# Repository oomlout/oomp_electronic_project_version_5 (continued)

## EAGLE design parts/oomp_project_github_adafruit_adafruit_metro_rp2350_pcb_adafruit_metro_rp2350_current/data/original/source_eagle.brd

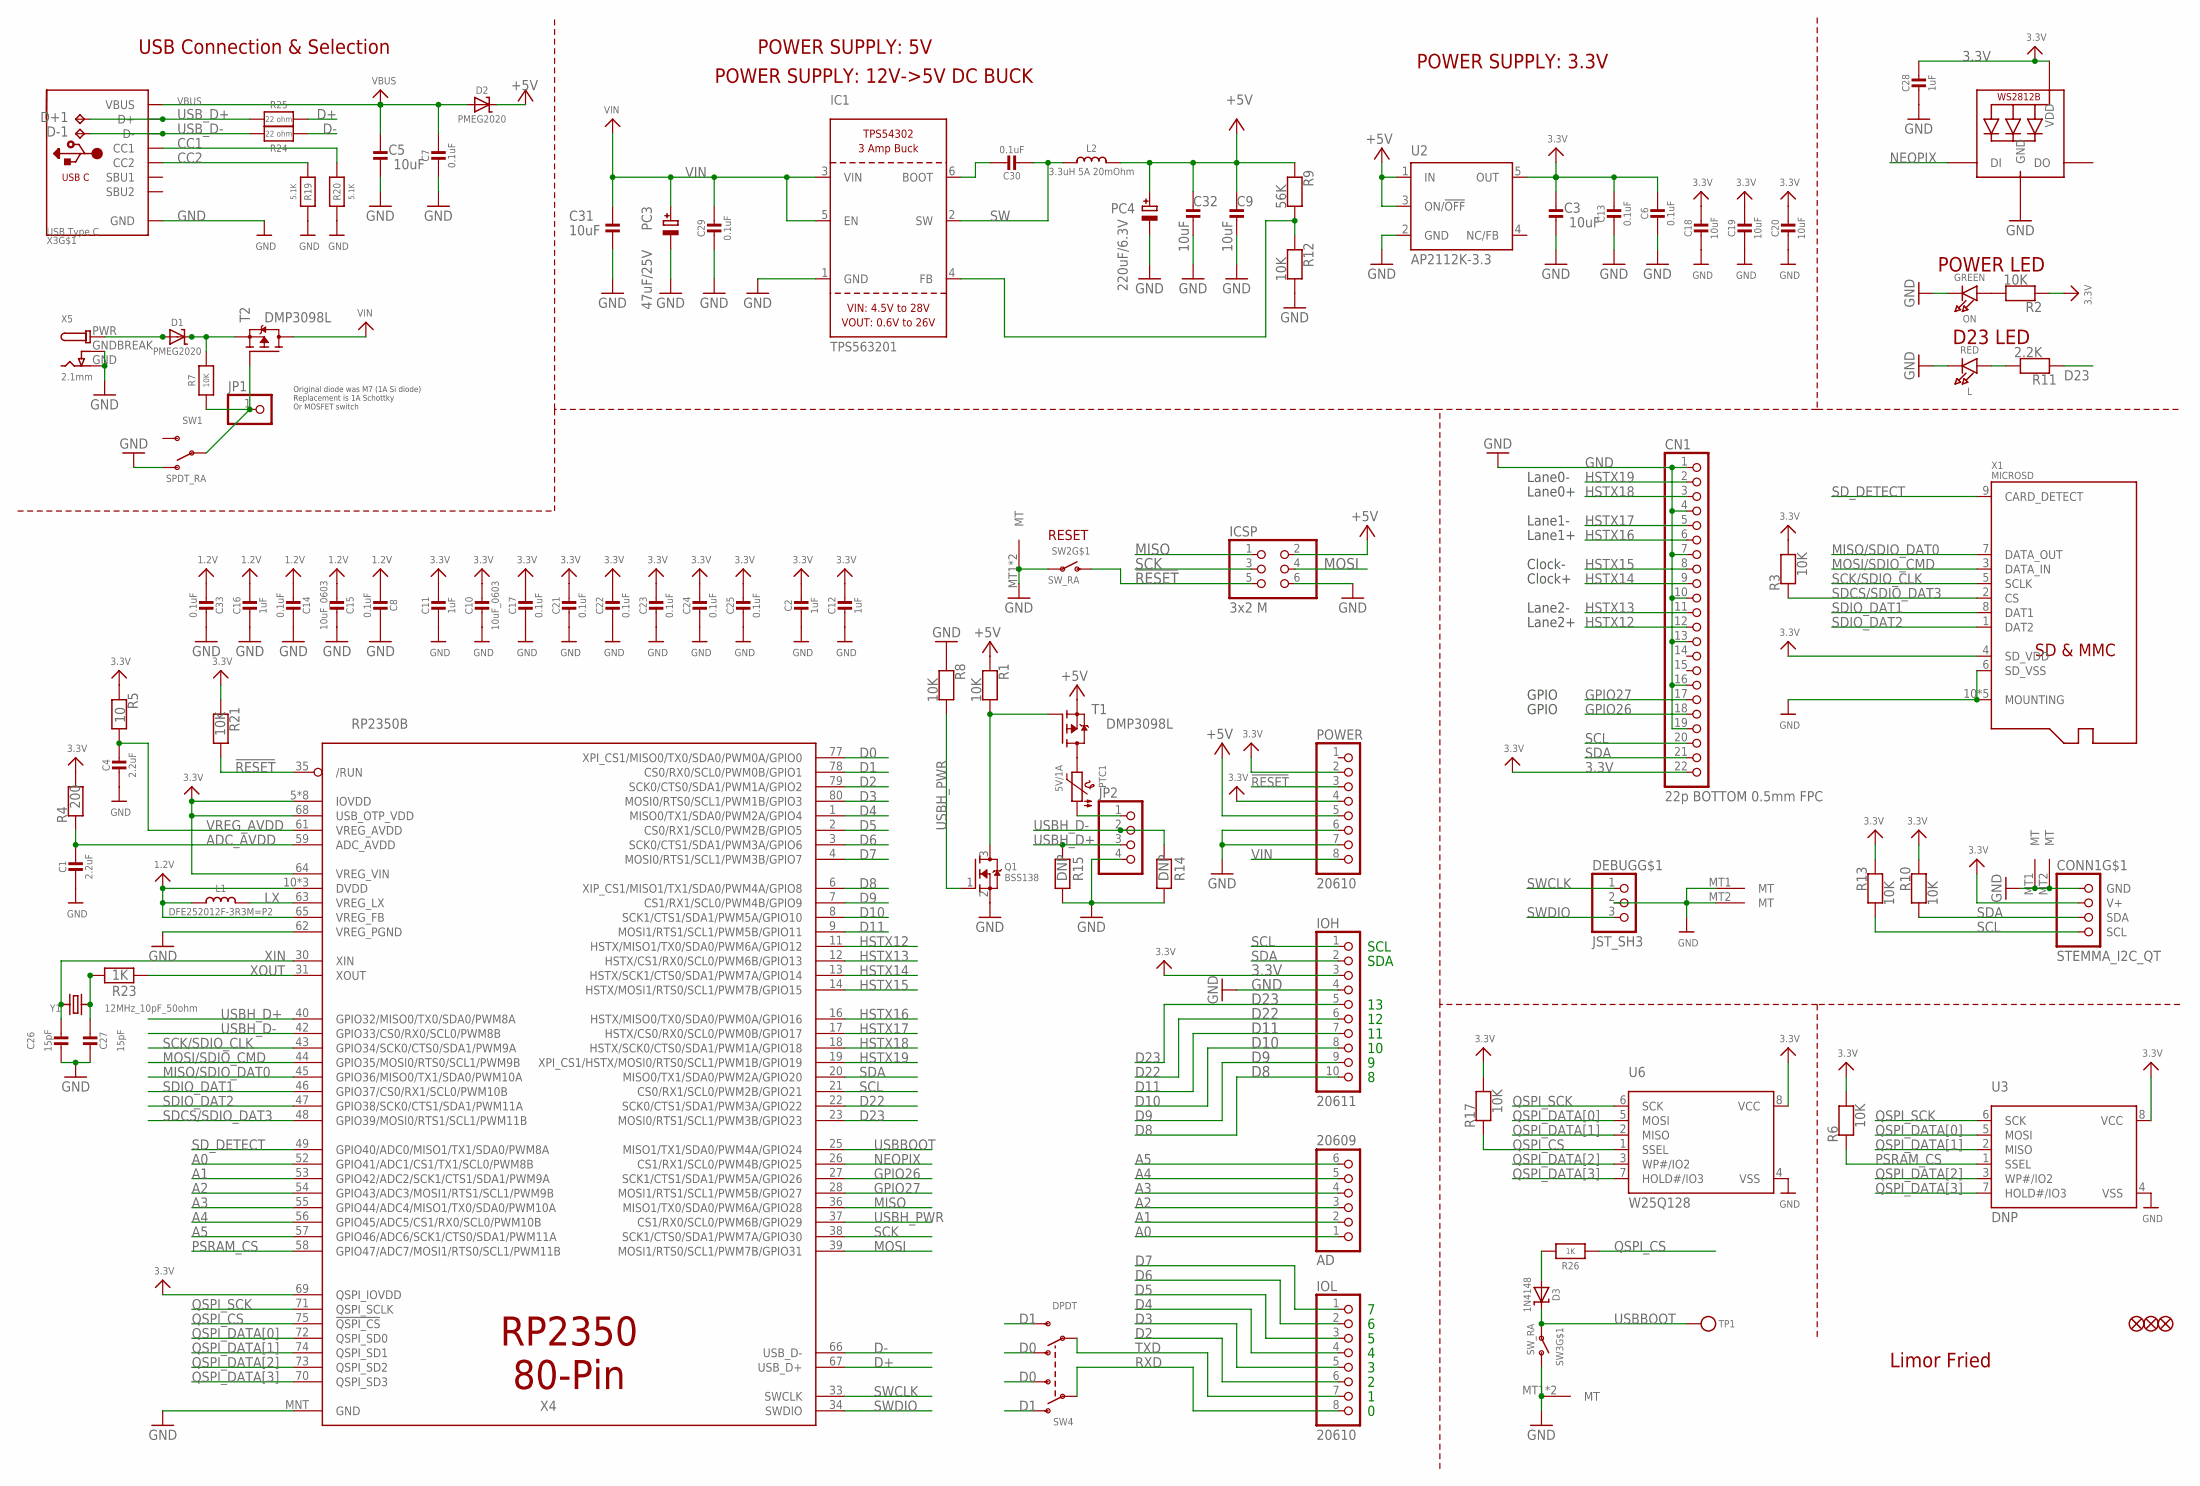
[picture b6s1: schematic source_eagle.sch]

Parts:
AD: 20609; 1X06_OVALWAVE
C1, C4: 2.2uF; 0603-NO
C2, C11, C12, C16, C28: 1uF; 0603-NO
C3, C5, C9, C18, C19, C20, C31, C32: 10uF; 0805-NO
C6, C7, C8, C13, C14, C17, C21, C22, C23, C24, C25, C29, C30, C33: 0.1uF; 0603-NO
C10, C15: 10uF_0603; 0603-NO_WIDE
C26, C27: 15pF; 0603-NO
CN1: 22p BOTTOM 0.5mm FPC; FPC_22PIN
CONN1: STEMMA_I2C_QT; JST_SH4
D1, D2: PMEG2020; SOD-323
D3: 1N4148; SOD-323
D+1: TPB1,27; B1,27
D-1: TPB1,27; B1,27
DEBUG: JST_SH3; JST_SH3_RA
FD1, FD2, FD3: FIDUCIAL_1MM
IC1: TPS563201; SOT23-6
ICSP: 3x2 M; 2X03_ROUND_70MIL
IOH: 20611; 1X10_OVALWAVE
IOL: 20610; 1X08_OVALWAVE
JP1: HEADER-1X1ROUND; 1X01_ROUND
JP2: HEADER-1X4ROUND; 1X04_ROUND
L: RED; CHIPLED_0603_NOOUTLINE
L1: DFE252012F-3R3M=P2; INDUCTOR_1007
L2: 3.3uH 5A 20mOhm; INDUCTOR_0603S
LED2: WS2812B_3535FULL; LED3535_FULLPADS
ON: GREEN; CHIPLED_0603_NOOUTLINE
PC3: 47uF/25V; PANASONIC_D
PC4: 220uF/6.3V; PANASONIC_D
POWER: 20610; 1X08_OVALWAVE
PTC1: 5V/1A; 0805-NO
Q1: BSS138; SOT23-WIDE
R1, R2, R3, R6, R7, R8, R10, R12, R13, R17, R21: 10K; 0603-NO
R4: 200; 0603-NO
R5: 10; 0603-NO
R9: 56K; 0603-NO
R11: 2.2K; 0603-NO
R14, R15: DNP; 0603-NO
R19, R20: 5.1K; 0603-NO
R23, R26: 1K; 0603-NO
R24, R25: 22 ohm; 0603-NO
SW1: SPDT_RA; SPDT_SMT_SSSS811101
SW2, SW3: SW_RA; SPST_TACTILE_RA
SW4: DPDT; EG1390
T1, T2: DMP3098L; SOT23-WIDE
TP1: TESTPOINTROUND1.5MMNO; TESTPOINT_ROUND_1.5MM_NO
U2: AP2112K-3.3; SOT23-DBV
U3: DNP; SOIC8_208MIL
U6: W25Q128; SOIC8_208MIL
X1: MICROSD; MOLEX_104031-0811
X3: USB Type C; USB_C_CUSB31-CFM2AX-01-X
X4: RP2350B; QFN80
X5: 2.1mm; DCJACK_2MM_PTH
Y1: 12MHz_10pF_50ohm; CRYSTAL_2.5X2

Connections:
1.2V: C8.2, C14.2, C15.2, C16.1, C33.2, L1.P$1 (1), X4.10 (DVDD), X4.32 (DVDD), X4.51 (DVDD), X4.65 (VREG_FB)
3.3V: C2.1, C3.2, C6.2, C10.1, C11.1, C12.1, C13.1, C17.1, C18.1, C19.1, C20.1, C21.1, C22.1, C23.1, C24.1, C25.1, C28.1, CN1.22, CONN1.2 (V+), IOH.3, LED2.2 (VDD), POWER.2, POWER.4, R2.1, R3.2, R4.2, R5.1, R6.2, R10.1, R13.1, R17.2, R21.1, U2.5 (OUT), U3.8 (VCC), U6.8 (VCC), X1.4 (SD_VDD), X4.5 (IOVDD), X4.15 (IOVDD), X4.24 (IOVDD), X4.29 (IOVDD), X4.41 (IOVDD), X4.50 (IOVDD), X4.60 (IOVDD), X4.64 (VREG_VIN), X4.68 (USB_OTP_VDD), X4.69 (QSPI_IOVDD), X4.76 (IOVDD)
!RESET: ICSP.5, POWER.3, R21.2, SW2.2 (S), X4.35 (/RUN)
+5V: C9.2, C32.2, D2.C, ICSP.2, L2.P$2 (2), PC4.+, POWER.5, R1.1, R9.1, T1.2 (S), U2.1 (IN), U2.3 (ON/!OFF)
A0: AD.1, X4.52 (GPIO41/ADC1/CS1/TX1/SCL0/PWM8B)
A1: AD.2, X4.53 (GPIO42/ADC2/SCK1/CTS1/SDA1/PWM9A)
A2: AD.3, X4.54 (GPIO43/ADC3/MOSI1/RTS1/SCL1/PWM9B)
A3: AD.4, X4.55 (GPIO44/ADC4/MISO1/TX0/SDA0/PWM10A)
A4: AD.5, X4.56 (GPIO45/ADC5/CS1/RX0/SCL0/PWM10B)
A5: AD.6, X4.57 (GPIO46/ADC6/SCK1/CTS0/SDA1/PWM11A)
ADC_AVDD: C1.1, R4.1, X4.59 (ADC_AVDD)
CC1: R20.2, X3.A5 (CC1)
CC2: R19.2, X3.B5 (CC2)
D0: SW4.O2, SW4.S1, X4.77 (XPI_CS1/MISO0/TX0/SDA0/PWM0A/GPIO0)
D1: SW4.O1, SW4.S2, X4.78 (CS0/RX0/SCL0/PWM0B/GPIO1)
D2: IOL.6, X4.79 (SCK0/CTS0/SDA1/PWM1A/GPIO2)
D3: IOL.5, X4.80 (MOSI0/RTS0/SCL1/PWM1B/GPIO3)
D4: IOL.4, X4.1 (MISO0/TX1/SDA0/PWM2A/GPIO4)
D5: IOL.3, X4.2 (CS0/RX1/SCL0/PWM2B/GPIO5)
D6: IOL.2, X4.3 (SCK0/CTS1/SDA1/PWM3A/GPIO6)
D7: IOL.1, X4.4 (MOSI0/RTS1/SCL1/PWM3B/GPIO7)
D8: IOH.10, X4.6 (XIP_CS1/MISO1/TX1/SDA0/PWM4A/GPIO8)
D9: IOH.9, X4.7 (CS1/RX1/SCL0/PWM4B/GPIO9)
D10: IOH.8, X4.8 (SCK1/CTS1/SDA1/PWM5A/GPIO10)
D11: IOH.7, X4.9 (MOSI1/RTS1/SCL1/PWM5B/GPIO11)
D22: IOH.6, X4.22 (SCK0/CTS1/SDA1/PWM3A/GPIO22)
D23: IOH.5, R11.1, X4.23 (MOSI0/RTS1/SCL1/PWM3B/GPIO23)
D+: R25.2, X4.67 (USB_D+)
D-: R24.2, X4.66 (USB_D-)
GND: C1.2, C2.2, C3.1, C4.2, C5.1, C6.1, C7.2, C8.1, C9.1, C10.2, C11.2, C12.2, C13.2, C14.1, C15.1, C16.2, C17.2, C18.2, C19.2, C20.2, C21.2, C22.2, C23.2, C24.2, C25.2, C26.1, C27.1, C28.2, C29.2, C31.1, C32.1, C33.1, CN1.1, CN1.4, CN1.7, CN1.10, CN1.13, CN1.16, CN1.19, CONN1.1 (GND), CONN1.MT1 (MT), CONN1.MT2 (MT), DEBUG.2, DEBUG.MT1 (MT), DEBUG.MT2 (MT), IC1.1 (GND), ICSP.6, IOH.4, JP2.4, L.C, LED2.4 (GND), ON.C, PC3.-, PC4.-, POWER.6, POWER.7, Q1.2 (S), R8.1, R12.2, R14.1, R15.1, R19.1, R20.1, SW1.A (O), SW2.1, SW2.MT1 (MT), SW2.MT2 (MT), SW3.2 (S), SW3.MT1 (MT), SW3.MT2 (MT), U2.2 (GND), U3.4 (VSS), U6.4 (VSS), X1.6 (SD_VSS), X1.10 (MOUNTING), X1.G1 (MOUNTING), X1.G2 (MOUNTING), X1.G3 (MOUNTING), X1.G4 (MOUNTING), X3.A1B12 (GND), X3.B1A12 (GND), X4.62 (VREG_PGND), X4.MNT (GND), X5.GND, X5.GNDBREAK
GPIO26: CN1.18, X4.27 (SCK1/CTS1/SDA1/PWM5A/GPIO26)
GPIO27: CN1.17, X4.28 (MOSI1/RTS1/SCL1/PWM5B/GPIO27)
HSTX12: CN1.12, X4.11 (HSTX/MISO1/TX0/SDA0/PWM6A/GPIO12)
HSTX13: CN1.11, X4.12 (HSTX/CS1/RX0/SCL0/PWM6B/GPIO13)
HSTX14: CN1.9, X4.13 (HSTX/SCK1/CTS0/SDA1/PWM7A/GPIO14)
HSTX15: CN1.8, X4.14 (HSTX/MOSI1/RTS0/SCL1/PWM7B/GPIO15)
HSTX16: CN1.6, X4.16 (HSTX/MISO0/TX0/SDA0/PWM0A/GPIO16)
HSTX17: CN1.5, X4.17 (HSTX/CS0/RX0/SCL0/PWM0B/GPIO17)
HSTX18: CN1.3, X4.18 (HSTX/SCK0/CTS0/SDA1/PWM1A/GPIO18)
HSTX19: CN1.2, X4.19 (XPI_CS1/HSTX/MOSI0/RTS0/SCL1/PWM1B/GPIO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)
LX: L1.P$2 (2), X4.63 (VREG_LX)
MISO: ICSP.1, X4.36 (MISO1/TX0/SDA0/PWM6A/GPIO28)
MISO/SDIO_DAT0: X1.7 (DATA_OUT), X4.45 (GPIO36/MISO0/TX1/SDA0/PWM10A)
MOSI: ICSP.4, X4.39 (MOSI1/RTS0/SCL1/PWM7B/GPIO31)
MOSI/SDIO_CMD: X1.3 (DATA_IN), X4.44 (GPIO35/MOSI0/RTS0/SCL1/PWM9B)
unnamed: L.A, R11.2
unnamed: ON.A, R2.2
unnamed: JP2.1, PTC1.1
unnamed: PTC1.2, T1.3 (D)
unnamed: Q1.3 (D), R1.2, T1.1 (G)
unnamed: D3.A, R26.2
unnamed: C30.1, IC1.6 (BOOT)
unnamed: IC1.4 (FB), R9.2, R12.1
unnamed: C27.2, R23.1, Y1.3 (2)
unnamed: D1.C, R7.2, T2.2 (S)
NEOPIX: LED2.1 (DI), X4.26 (CS1/RX1/SCL0/PWM4B/GPIO25)
PSRAM_CS: R6.1, U3.1 (SSEL), X4.58 (GPIO47/ADC7/MOSI1/RTS0/SCL1/PWM11B)
PWRIN: D1.A, X5.PWR
PWR_SWITCH: JP1.1, R7.1, SW1.B, T2.1 (G)
QSPI_CS: R17.1, R26.1, U6.1 (SSEL), X4.75 (!QSPI_CS)
QSPI_DATA[0]: U3.5 (MOSI), U6.5 (MOSI), X4.72 (QSPI_SD0)
QSPI_DATA[1]: U3.2 (MISO), U6.2 (MISO), X4.74 (QSPI_SD1)
QSPI_DATA[2]: U3.3 (WP#/IO2), U6.3 (WP#/IO2), X4.73 (QSPI_SD2)
QSPI_DATA[3]: U3.7 (HOLD#/IO3), U6.7 (HOLD#/IO3), X4.70 (QSPI_SD3)
QSPI_SCK: U3.6 (SCK), U6.6 (SCK), X4.71 (QSPI_SCLK)
RXD: IOL.8, SW4.P1
SCK: ICSP.3, X4.38 (SCK1/CTS0/SDA1/PWM7A/GPIO30)
SCK/SDIO_CLK: X1.5 (SCLK), X4.43 (GPIO34/SCK0/CTS0/SDA1/PWM9A)
SCL: CN1.20, CONN1.4 (SCL), IOH.1, R13.2, X4.21 (CS0/RX1/SCL0/PWM2B/GPIO21)
SDA: CN1.21, CONN1.3 (SDA), IOH.2, R10.2, X4.20 (MISO0/TX1/SDA0/PWM2A/GPIO20)
SDCS/SDIO_DAT3: R3.1, X1.2 (CS), X4.48 (GPIO39/MOSI0/RTS1/SCL1/PWM11B)
SDIO_DAT1: X1.8 (DAT1), X4.46 (GPIO37/CS0/RX1/SCL0/PWM10B)
SDIO_DAT2: X1.1 (DAT2), X4.47 (GPIO38/SCK0/CTS1/SDA1/PWM11A)
SD_DETECT: X1.9 (CARD_DETECT), X4.49 (GPIO40/ADC0/MISO1/TX1/SDA0/PWM8A)
SW: C30.2, IC1.2 (SW), L2.P$1 (1)
SWCLK: DEBUG.1, X4.33 (SWCLK)
SWDIO: DEBUG.3, X4.34 (SWDIO)
TXD: IOL.7, SW4.P2
USBBOOT: D3.C, SW3.1, TP1.P$1, X4.25 (MISO1/TX1/SDA0/PWM4A/GPIO24)
USBH_D+: JP2.3, R15.2, X4.40 (GPIO32/MISO0/TX0/SDA0/PWM8A)
USBH_D-: JP2.2, R14.2, X4.42 (GPIO33/CS0/RX0/SCL0/PWM8B)
USBH_PWR: Q1.1 (G), R8.2, X4.37 (CS1/RX0/SCL0/PWM6B/GPIO29)
USB_D+: D+1.TP, R25.1, X3.A6 (D+), X3.B6 (D+)
USB_D-: D-1.TP, R24.1, X3.A7 (D-), X3.B7 (D-)
VBUS: C5.2, C7.1, D2.A, X3.A4B9 (VBUS), X3.B4A9 (VBUS)
VIN: C29.1, C31.2, IC1.3 (VIN), IC1.5 (EN), PC3.+, POWER.8, T2.3 (D)
VREG_AVDD: C4.1, R5.2, X4.61 (VREG_AVDD)
XIN: C26.2, X4.30 (XIN), Y1.1
XOUT: R23.2, X4.31 (XOUT)

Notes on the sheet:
SDA
SCL
Limor Fried
Original diode was M7 (1A Si diode) Replacement is 1A Schottky Or MOSFET switch
POWER SUPPLY: 5V
USB Connection & Selection
POWER SUPPLY: 3.3V
POWER LED
D23 LED
RESET
Lane0-
Lane0+
Lane1-
Lane1+
Clock-
Clock+
Lane2-
Lane2+
GPIO
POWER SUPPLY: 12V->5V DC BUCK

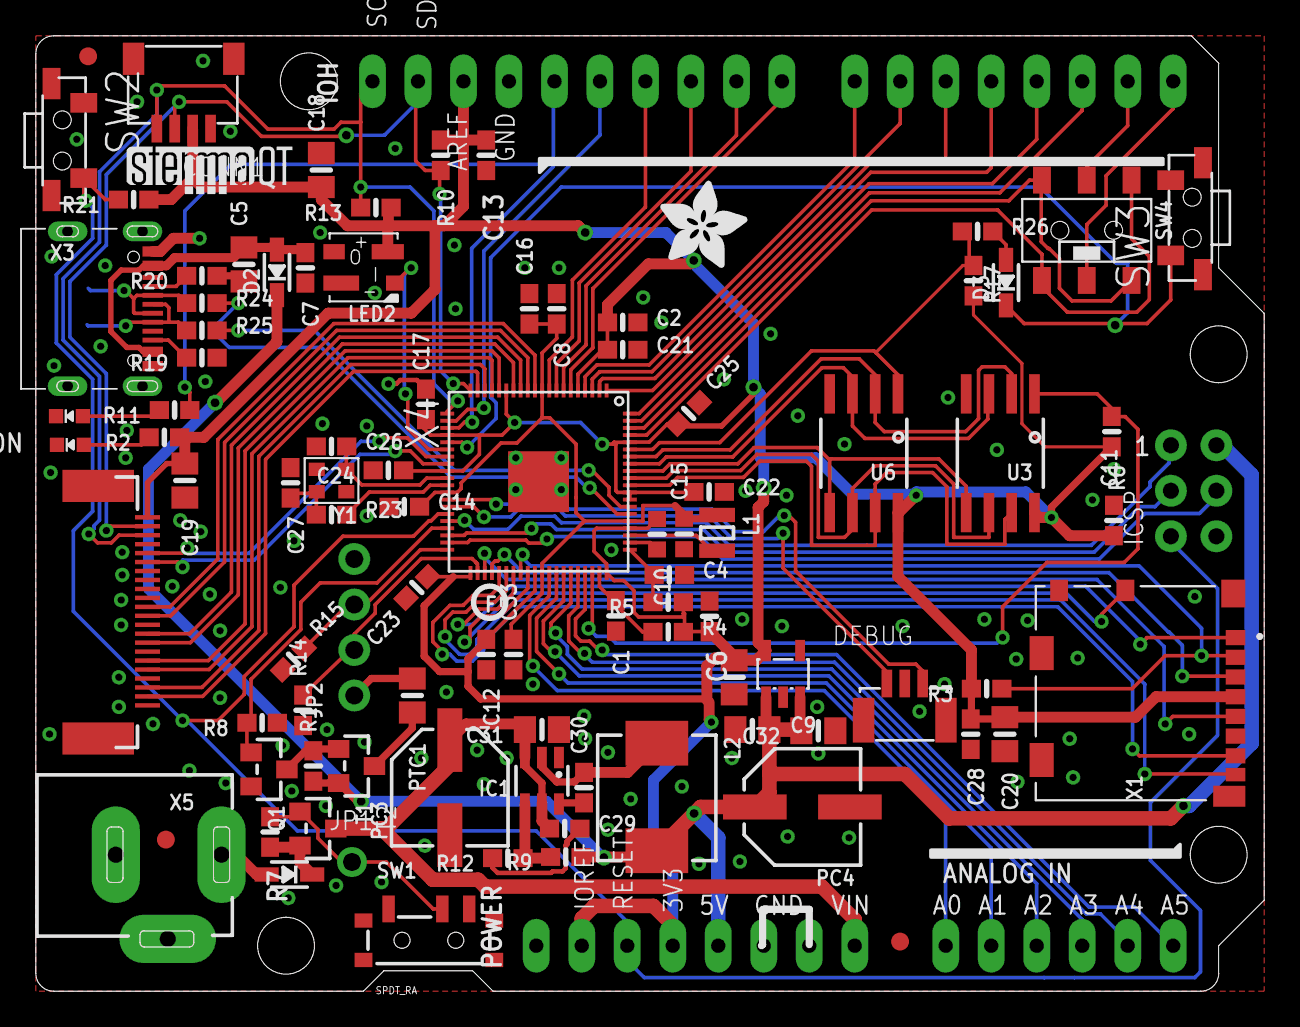
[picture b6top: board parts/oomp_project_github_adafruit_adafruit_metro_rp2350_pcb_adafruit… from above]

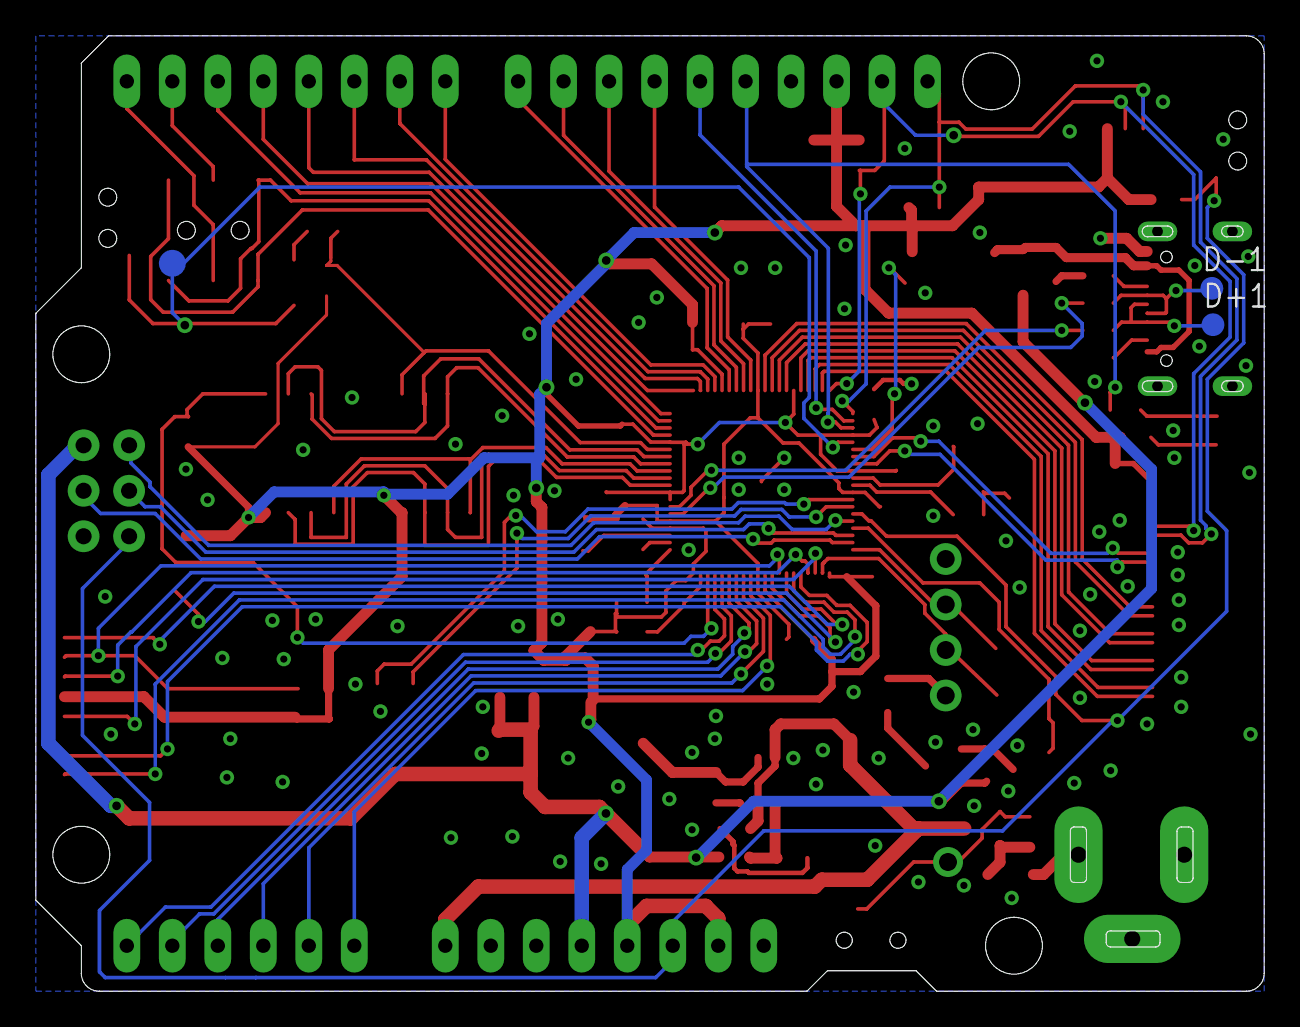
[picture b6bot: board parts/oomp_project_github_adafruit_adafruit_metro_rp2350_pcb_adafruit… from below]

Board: 2 copper layers, 68.6 x 53.3 mm, 170 parts (5 on the bottom side), 89 nets.

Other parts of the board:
PLABEL0: PLABEL0
PLABEL1: PLABEL1
PLABEL2: PLABEL2
PLABEL3: PLABEL3
PLABEL4: PLABEL4
PLABEL5: PLABEL5
PLABEL6: PLABEL6
PLABEL7: PLABEL7
PLABEL8: PLABEL8
PLABEL10: PLABEL10
PLABEL11: PLABEL11
PLABEL12: PLABEL12
PLABEL13: PLABEL13
PLABEL14: PLABEL14
PLABEL15: PLABEL15
PLABEL16: PLABEL16
PLABEL17: PLABEL17
PLABEL18: PLABEL18
PLABEL19: PLABEL19
PLABEL20: PLABEL20
PLABEL21: PLABEL21
PLABEL22: PLABEL22
PLABEL23: PLABEL23
PLABEL24: PLABEL24
PLABEL25: PLABEL25
PLABEL26: PLABEL26
PLABEL27: PLABEL27
PLABEL28: PLABEL28
PLABEL29: PLABEL29
PLABEL30: PLABEL30
PLABEL31: PLABEL31
PLABEL32: PLABEL32
PLABEL33: PLABEL33
PLABEL34: PLABEL34
PLABEL35: PLABEL35
PLABEL36: PLABEL36
PLABEL37: PLABEL37
PLABEL38: PLABEL38
PLABEL39: PLABEL39
PLABEL40: PLABEL40
PLABEL41: PLABEL41
PLABEL42: PLABEL42
PLABEL43: PLABEL43
PLABEL46: PLABEL46
PLABEL47: PLABEL47
PLABEL48: PLABEL48
PLABEL49: PLABEL49
PLABEL50: PLABEL50
PLABEL51: PLABEL51
PLABEL52: PLABEL52
PLABEL53: PLABEL53
PLABEL54: PLABEL54
PLABEL55: PLABEL55
PLABEL56: PLABEL56
PLABEL57: PLABEL57
PLABEL59: PLABEL59
PLABEL60: PLABEL60
PLABEL62: PLABEL62
PLABEL63: PLABEL63
PLABEL64: PLABEL64
PLABEL65: PLABEL65
PLABEL66: PLABEL66
PLABEL67: PLABEL67
PLABEL68: PLABEL68
PLABEL69: PLABEL69
PLABEL70: PLABEL70
U$3: STEMMAQT
U$11: PCBFEAT-REV-040
U$47: METRO_RP2350_TOP
U$50: ADAFRUIT_5MM
U$71: METRO_RP2350_BOT

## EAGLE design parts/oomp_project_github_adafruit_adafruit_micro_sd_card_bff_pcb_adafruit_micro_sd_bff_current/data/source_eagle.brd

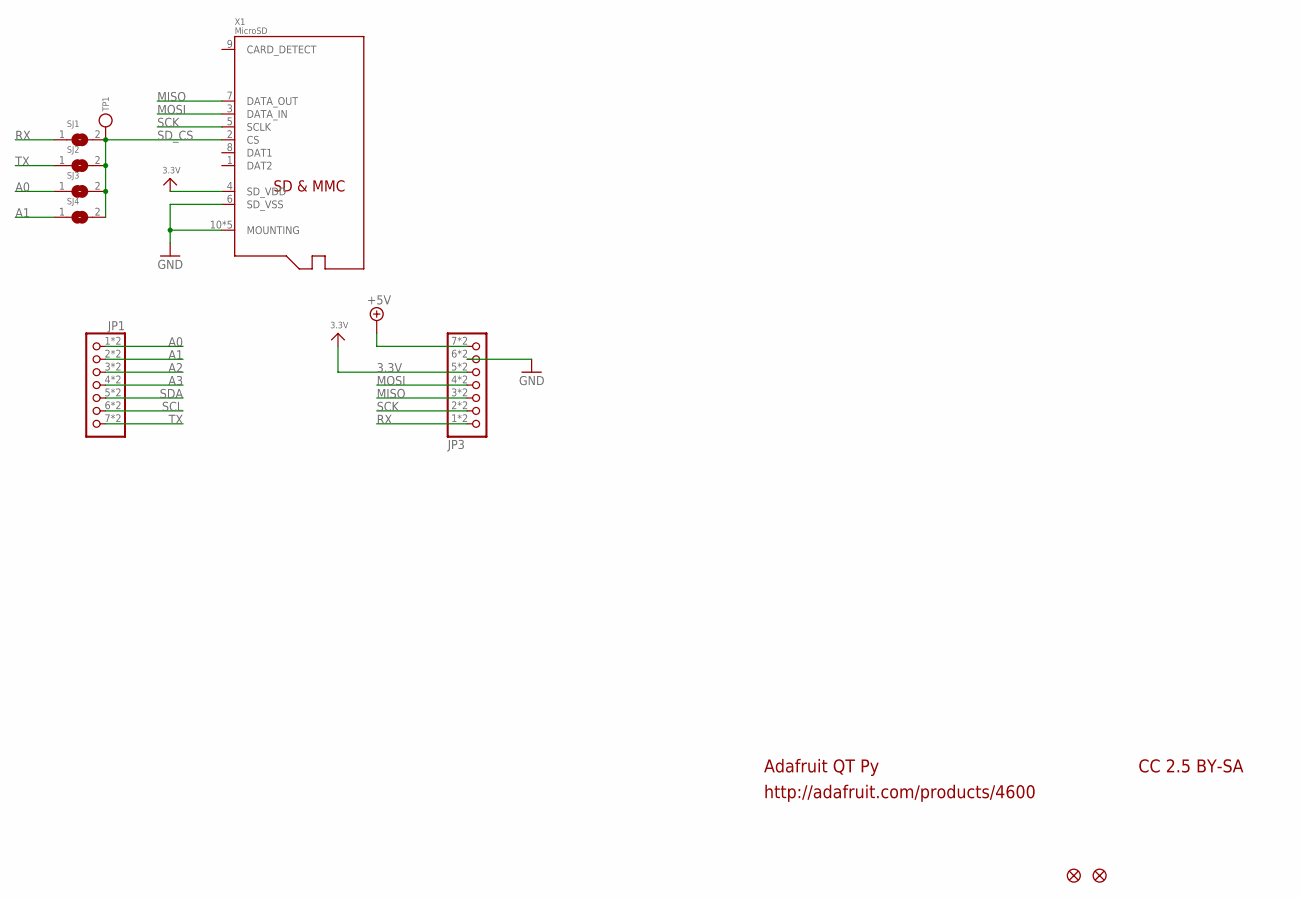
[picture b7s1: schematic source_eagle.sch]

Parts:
JP1, JP3: HEADER-1X7_CASTEL; 1X07_CASTEL
SJ1, SJ3, SJ4: SOLDERJUMPER; SOLDERJUMPER_ARROW_NOPASTE
SJ2: SOLDERJUMPERCLOSED; SOLDERJUMPER_CLOSEDWIRE
TP1: TESTPOINTPAD1MM; TESTPOINT_PAD_1MM
U$6, U$8: FIDUCIAL_1MM
X1: MicroSD; MOLEX_104031-0811

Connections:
3.3V: JP3.5, JP3.5C (5), X1.4 (SD_VDD)
+5V: JP3.7, JP3.7C (7)
A0: JP1.1, JP1.1C (1), SJ3.1
A1: JP1.2, JP1.2C (2), SJ4.1
A2: JP1.3, JP1.3C (3)
A3: JP1.4, JP1.4C (4)
GND: JP3.6, JP3.6C (6), X1.6 (SD_VSS), X1.10 (MOUNTING), X1.G1 (MOUNTING), X1.G2 (MOUNTING), X1.G3 (MOUNTING), X1.G4 (MOUNTING)
MISO: JP3.3, JP3.3C (3), X1.7 (DATA_OUT)
MOSI: JP3.4, JP3.4C (4), X1.3 (DATA_IN)
RX: JP3.1, JP3.1C (1), SJ1.1
SCK: JP3.2, JP3.2C (2), X1.5 (SCLK)
SCL: JP1.6, JP1.6C (6)
SDA: JP1.5, JP1.5C (5)
SD_CS: SJ1.2, SJ2.2, SJ3.2, SJ4.2, TP1.P$1, X1.2 (CS)
TX: JP1.7, JP1.7C (7), SJ2.1

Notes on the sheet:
Adafruit QT Py
http://adafruit.com/products/4600
CC 2.5 BY-SA

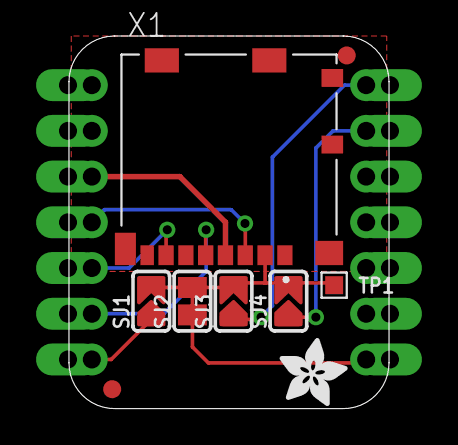
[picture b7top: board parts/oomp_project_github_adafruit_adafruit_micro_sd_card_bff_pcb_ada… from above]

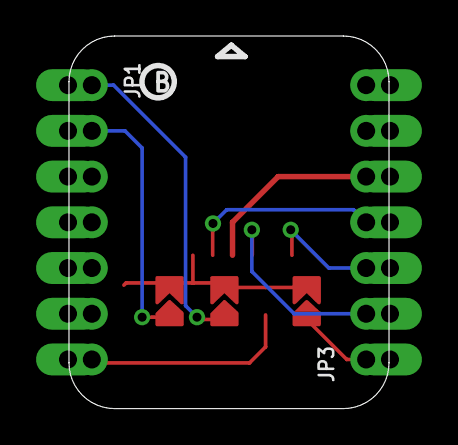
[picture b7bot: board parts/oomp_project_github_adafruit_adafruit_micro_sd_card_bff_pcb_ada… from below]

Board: 2 copper layers, 17.8 x 20.7 mm, 20 parts (5 on the bottom side), 15 nets.

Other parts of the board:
PLABEL0: PLABEL0
PLABEL1: PLABEL1
PLABEL2: PLABEL2
PLABEL3: PLABEL3
PLABEL4: PLABEL4
PLABEL5: PLABEL5
PLABEL6: PLABEL6
PLABEL7: PLABEL7
U$2: ADAFRUIT_3.5MM
U$3: PCBFEAT-REV-040

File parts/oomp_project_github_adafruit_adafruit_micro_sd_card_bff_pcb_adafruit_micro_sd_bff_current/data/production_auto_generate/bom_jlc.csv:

Comment,Designator,Footprint,LCSC Part #
,"JP1,JP3",Adafruit microSD BFF-import-fps:1X07_CASTEL,C7501585
,U$2,Adafruit microSD BFF-import-fps:ADAFRUIT_3.5MM,
,U$3,Adafruit microSD BFF-import-fps:PCBFEAT-REV-040,
,PLABEL0,Adafruit microSD BFF-import-fps:PLABEL0,
,PLABEL1,Adafruit microSD BFF-import-fps:PLABEL1,
,PLABEL2,Adafruit microSD BFF-import-fps:PLABEL2,
,PLABEL3,Adafruit microSD BFF-import-fps:PLABEL3,
,PLABEL4,Adafruit microSD BFF-import-fps:PLABEL4,
,PLABEL5,Adafruit microSD BFF-import-fps:PLABEL5,
,PLABEL6,Adafruit microSD BFF-import-fps:PLABEL6,
,PLABEL7,Adafruit microSD BFF-import-fps:PLABEL7,
,TP1,Adafruit microSD BFF-import-fps:TESTPOINT_PAD_1MM,
FIDUCIAL_1MM,"U$6,U$8",Adafruit microSD BFF-import-fps:FIDUCIAL_1MM,
MicroSD,X1,Adafruit microSD BFF-import-fps:MOLEX_104031-0811,

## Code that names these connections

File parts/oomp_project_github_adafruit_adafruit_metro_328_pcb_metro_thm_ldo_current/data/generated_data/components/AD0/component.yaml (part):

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      connected_to:
      - reference: ZU4
        pin_number: '23'
        pin_name: (ADC0)PC0)
    - number: '2'
      name: '2'
      electrical_type: passive
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      connected_to:
      - reference: ZU4
        pin_number: '24'
        pin_name: (ADC1)PC1
    - number: '3'
      name: '3'
      electrical_type: passive
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      connected_to:
      - reference: ZU4
        pin_number: '25'
        pin_name: (ADC2)PC2
    - number: '4'
      name: '4'
      electrical_type: passive
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      connected_to:
      - reference: ZU4
        pin_number: '26'
        pin_name: (ADC3)PC3
    - number: '5'
      name: '5'
      electrical_type: passive
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        pin_name: '2'
      - reference: ZU4
        pin_number: '27'
        pin_name: (ADC4)PC4
    - number: '6'
      name: '6'
      electrical_type: passive
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        pin_name: '1'
      - reference: ZU4
        pin_number: '28'
        pin_name: (ADC5)PC5
    size:
      local_graphics:
        measurement: symbol graphics only; excludes pins, properties, and text
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    pin_name: '2'
  - reference: ZU4
    pin_number: '23'
    pin_name: (ADC0)PC0)
  - reference: ZU4
    pin_number: '24'
    pin_name: (ADC1)PC1
  - reference: ZU4
    pin_number: '25'
    pin_name: (ADC2)PC2
  - reference: ZU4
    pin_number: '26'
    pin_name: (ADC3)PC3
  - reference: ZU4
    pin_number: '27'
    pin_name: (ADC4)PC4
  - reference: ZU4
    pin_number: '28'
    pin_name: (ADC5)PC5
pcb:
  reference: AD0
  value: '20609'
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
